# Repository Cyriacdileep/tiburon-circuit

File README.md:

CIRCUIT EXPLANATION
This project implements a dual-input power redundancy circuit using two LM5050-1 ideal diode controllers and two N-channel MOSFETs. The purpose of the circuit is to allow two power sources (VIN1 and VIN2) to supply a common output (VOUT).
Each LM5050-1 controls a MOSFET. When an input source is available, the controller turns on the MOSFET and allows power to flow to the output with very low voltage drop.
If one input source fails or drops below the output voltage, the LM5050-1 turns off the MOSFET to prevent reverse current from flowing back into that source.
This ensures that the load connected to VOUT continues to receive power as long as at least one input source is active.

MOSFET SELECTION
The SUM40N10-30 N-channel MOSFET was selected for this design.
It has a low RDS(on), which helps reduce power loss and heat dissipation during operation.
The MOSFET also has a suitable gate threshold voltage, allowing it to be driven effectively by the LM5050-1.
Also this one was used in the example application circuit in the datasheet.

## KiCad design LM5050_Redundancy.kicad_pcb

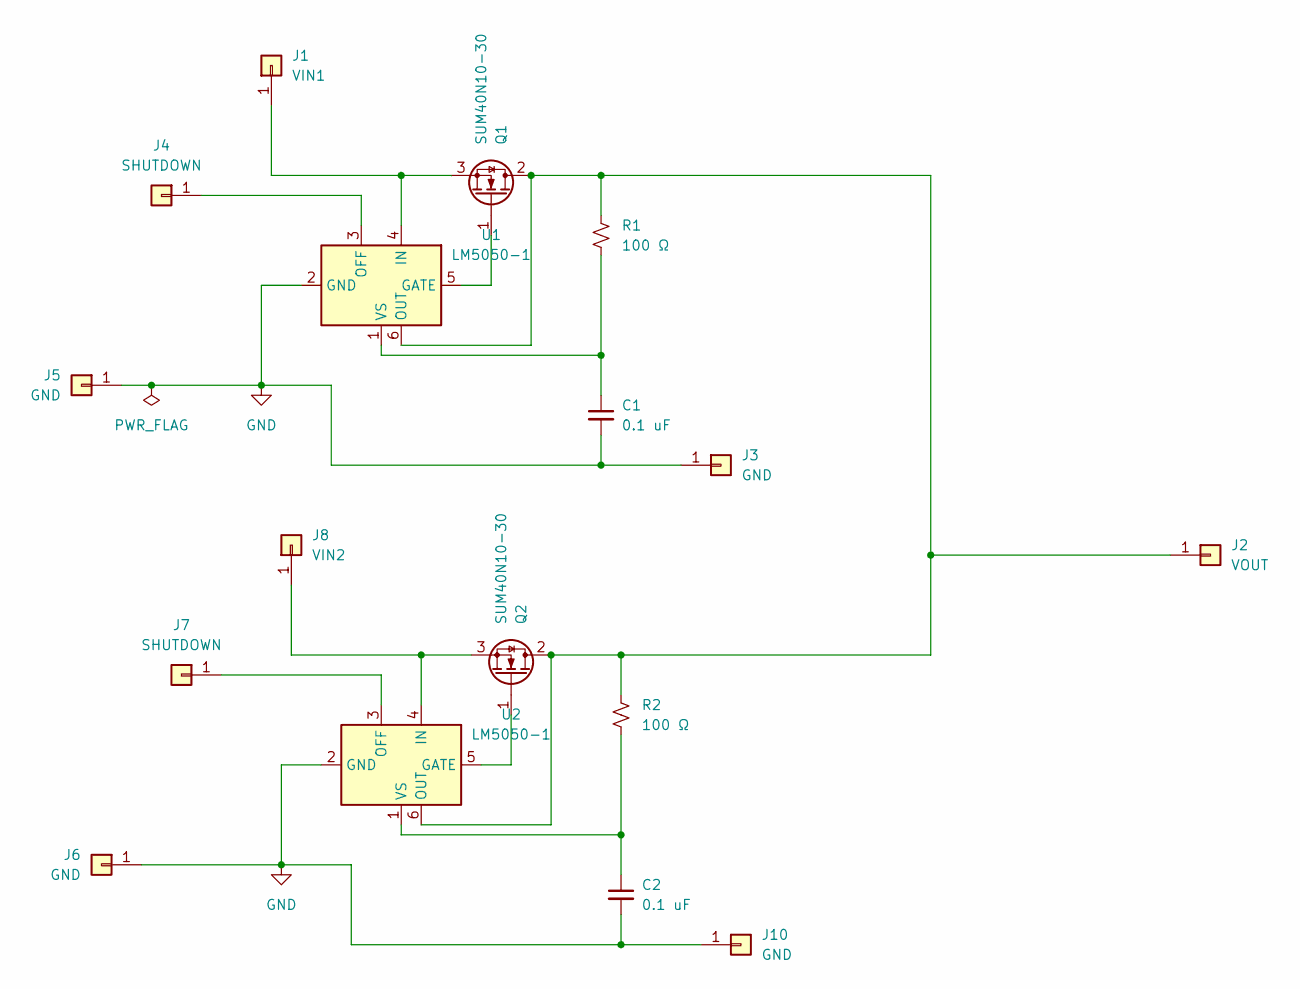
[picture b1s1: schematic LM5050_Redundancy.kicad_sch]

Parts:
C1, C2: 0.1 uF; C_0805_2012Metric
J1: VIN1; PinHeader_1x01_P2.54mm_Vertical
J2: VOUT; PinHeader_1x01_P2.54mm_Vertical
J3, J5, J6, J10: GND; PinHeader_1x01_P2.54mm_Vertical
J4, J7: SHUTDOWN; PinHeader_1x01_P2.54mm_Vertical
J8: VIN2; PinHeader_1x01_P2.54mm_Vertical
Q1, Q2: SUM40N10-30; TO-263-3_TabPin2
R1, R2: 100 Ω; R_0805_2012Metric
U1, U2: LM5050-1; TSOT-23-6

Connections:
GND: C1.2, C2.2, J3.1 (Pin_1_1), J5.1 (Pin_1_1), J6.1 (Pin_1_1), J10.1 (Pin_1_1), U1.2 (GND), U2.2 (GND)
unnamed: J1.1 (Pin_1_1), Q1.3 (S), U1.4 (IN)
unnamed: J2.1 (Pin_1_1), Q1.2 (D), Q2.2 (D), R1.1, R2.1, U1.6 (OUT), U2.6 (OUT)
unnamed: J4.1 (Pin_1_1), U1.3 (OFF)
unnamed: J7.1 (Pin_1_1), U2.3 (OFF)
unnamed: J8.1 (Pin_1_1), Q2.3 (S), U2.4 (IN)
unnamed: Q1.1 (G), U1.5 (GATE)
unnamed: Q2.1 (G), U2.5 (GATE)
unnamed: C1.1, R1.2, U1.1 (VS)
unnamed: C2.1, R2.2, U2.1 (VS)

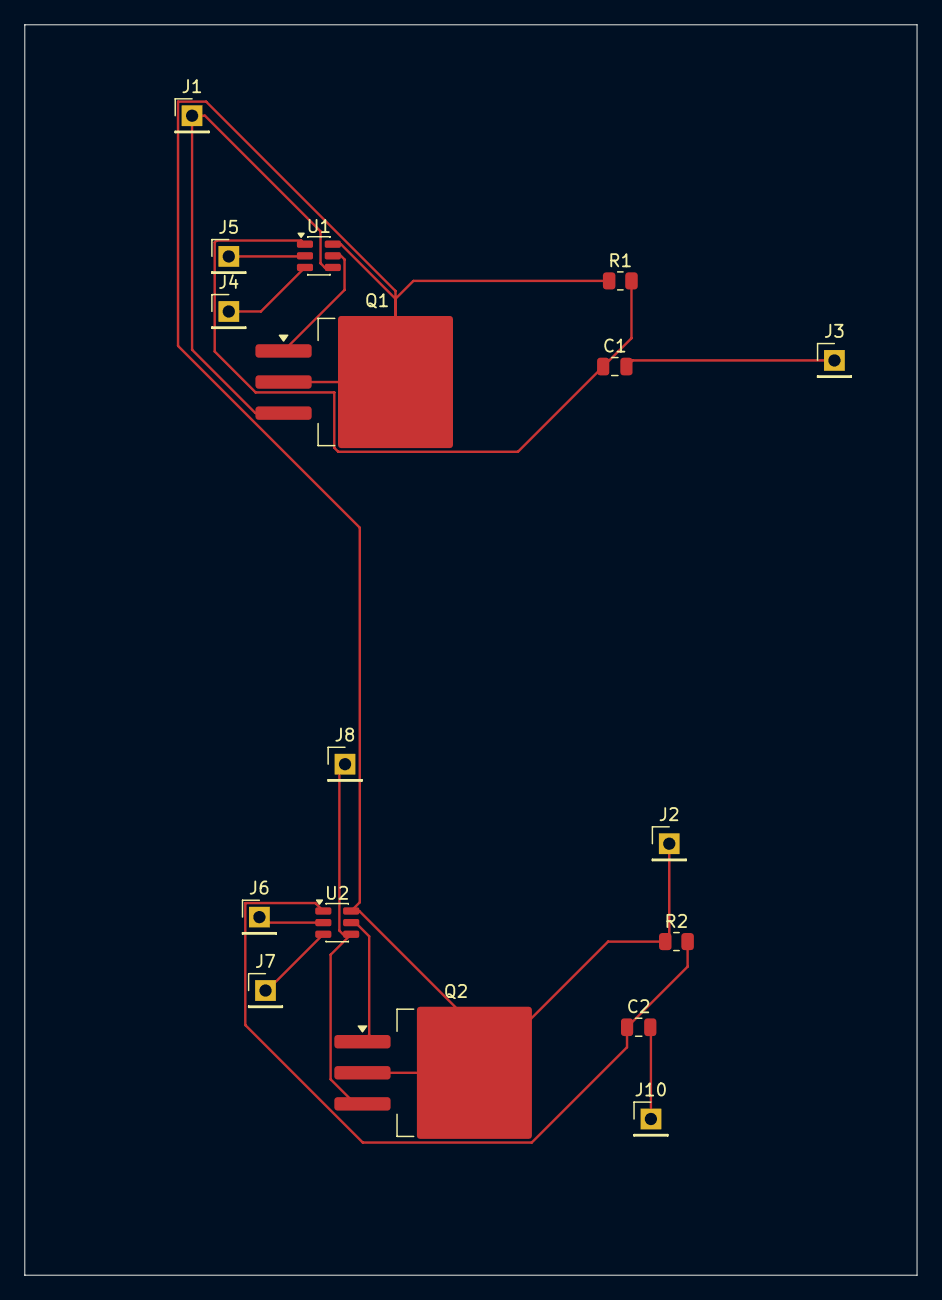
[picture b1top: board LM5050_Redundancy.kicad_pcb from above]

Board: 2 copper layers, 72.9 x 102.2 mm, 17 parts (0 on the bottom side), 10 nets.

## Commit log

2026-06-06 add LM5050 and MOSFET symbol
2026-06-06 create single LM5050 power path
2026-06-08 Complete dual input redundancy schematic
2026-06-08 Assign footprints and ERC
2026-06-08 finish routing and DRC
